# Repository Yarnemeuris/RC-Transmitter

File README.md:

# RC Transmitter

This is an RC Transmitter for controlling things like planes or cars. It's made with a rp2040 microcontroller and a nRf24 ic for the wireless comunication.

## CAD
The transmitter is fully 3D printed and uses about 80g of filament. The parts required for assembly are in the BOM. To assemble it you place M3 nuts and add a screw through them. It was fully designed in onshape, so [you can view it](https://cad.onshape.com/documents/07641ffae3f4ad45f3c4466a/w/8f5604270294a6fafcbc2443/e/dfa80ad51705840b5752194c?renderMode=0&uiState=69ac4f1de3e454b85e083a43).

## PCB
In the transmitter are 2 PCBs. One is a 2 layer board for all the wireless things. The same board can be used to recieve the signals, so you need at least 2 of these.

The other one is 4 layers and has everything else on it: the input, microcontroller, battery management. 

## Firmware
The firmware is setup to transmit everythingvia the second core of the rp2040. This makes sure that it's always available to transmit. The main core does everything else, like drawing to the screen and comunicating with the other ICs. Because this happends on a seperate core, a long I²C message won't stop the transmission. Flashing the board can be done by shorting the two program pads while booting the board, and flashing the [uf2 file](https://github.com/Yarnemeuris/RC-Transmitter/blob/main/Firmware/Firmware.uf2) via the USb connection.

## BOM
This is the simplified BOM. You can find the full and other BOMs [here](https://github.com/Yarnemeuris/RC-Transmitter/tree/main/BOM).

|Category  |Item           |Quantity|Unit Price|Total Price|Running Total|
|----------|---------------|--------|----------|-----------|-------------|
|Components|LCSC Components|1       |$43.52    |$43.52     |$43.52       |
|Components|LCSC Shipping  |1       |$11.44    |$11.44     |$54.96       |
|PCB       |RF PCB         |1       |$2.10     |$2.10      |$57.06       |
|PCB       |Main PCB       |1       |$7.00     |$7.00      |$64.06       |
|PCB       |Stencil        |1       |$12.00    |$12.00     |$76.06       |
|PCB       |JLCPCB Shipping|1       |$20.15    |$20.15     |$96.21       |

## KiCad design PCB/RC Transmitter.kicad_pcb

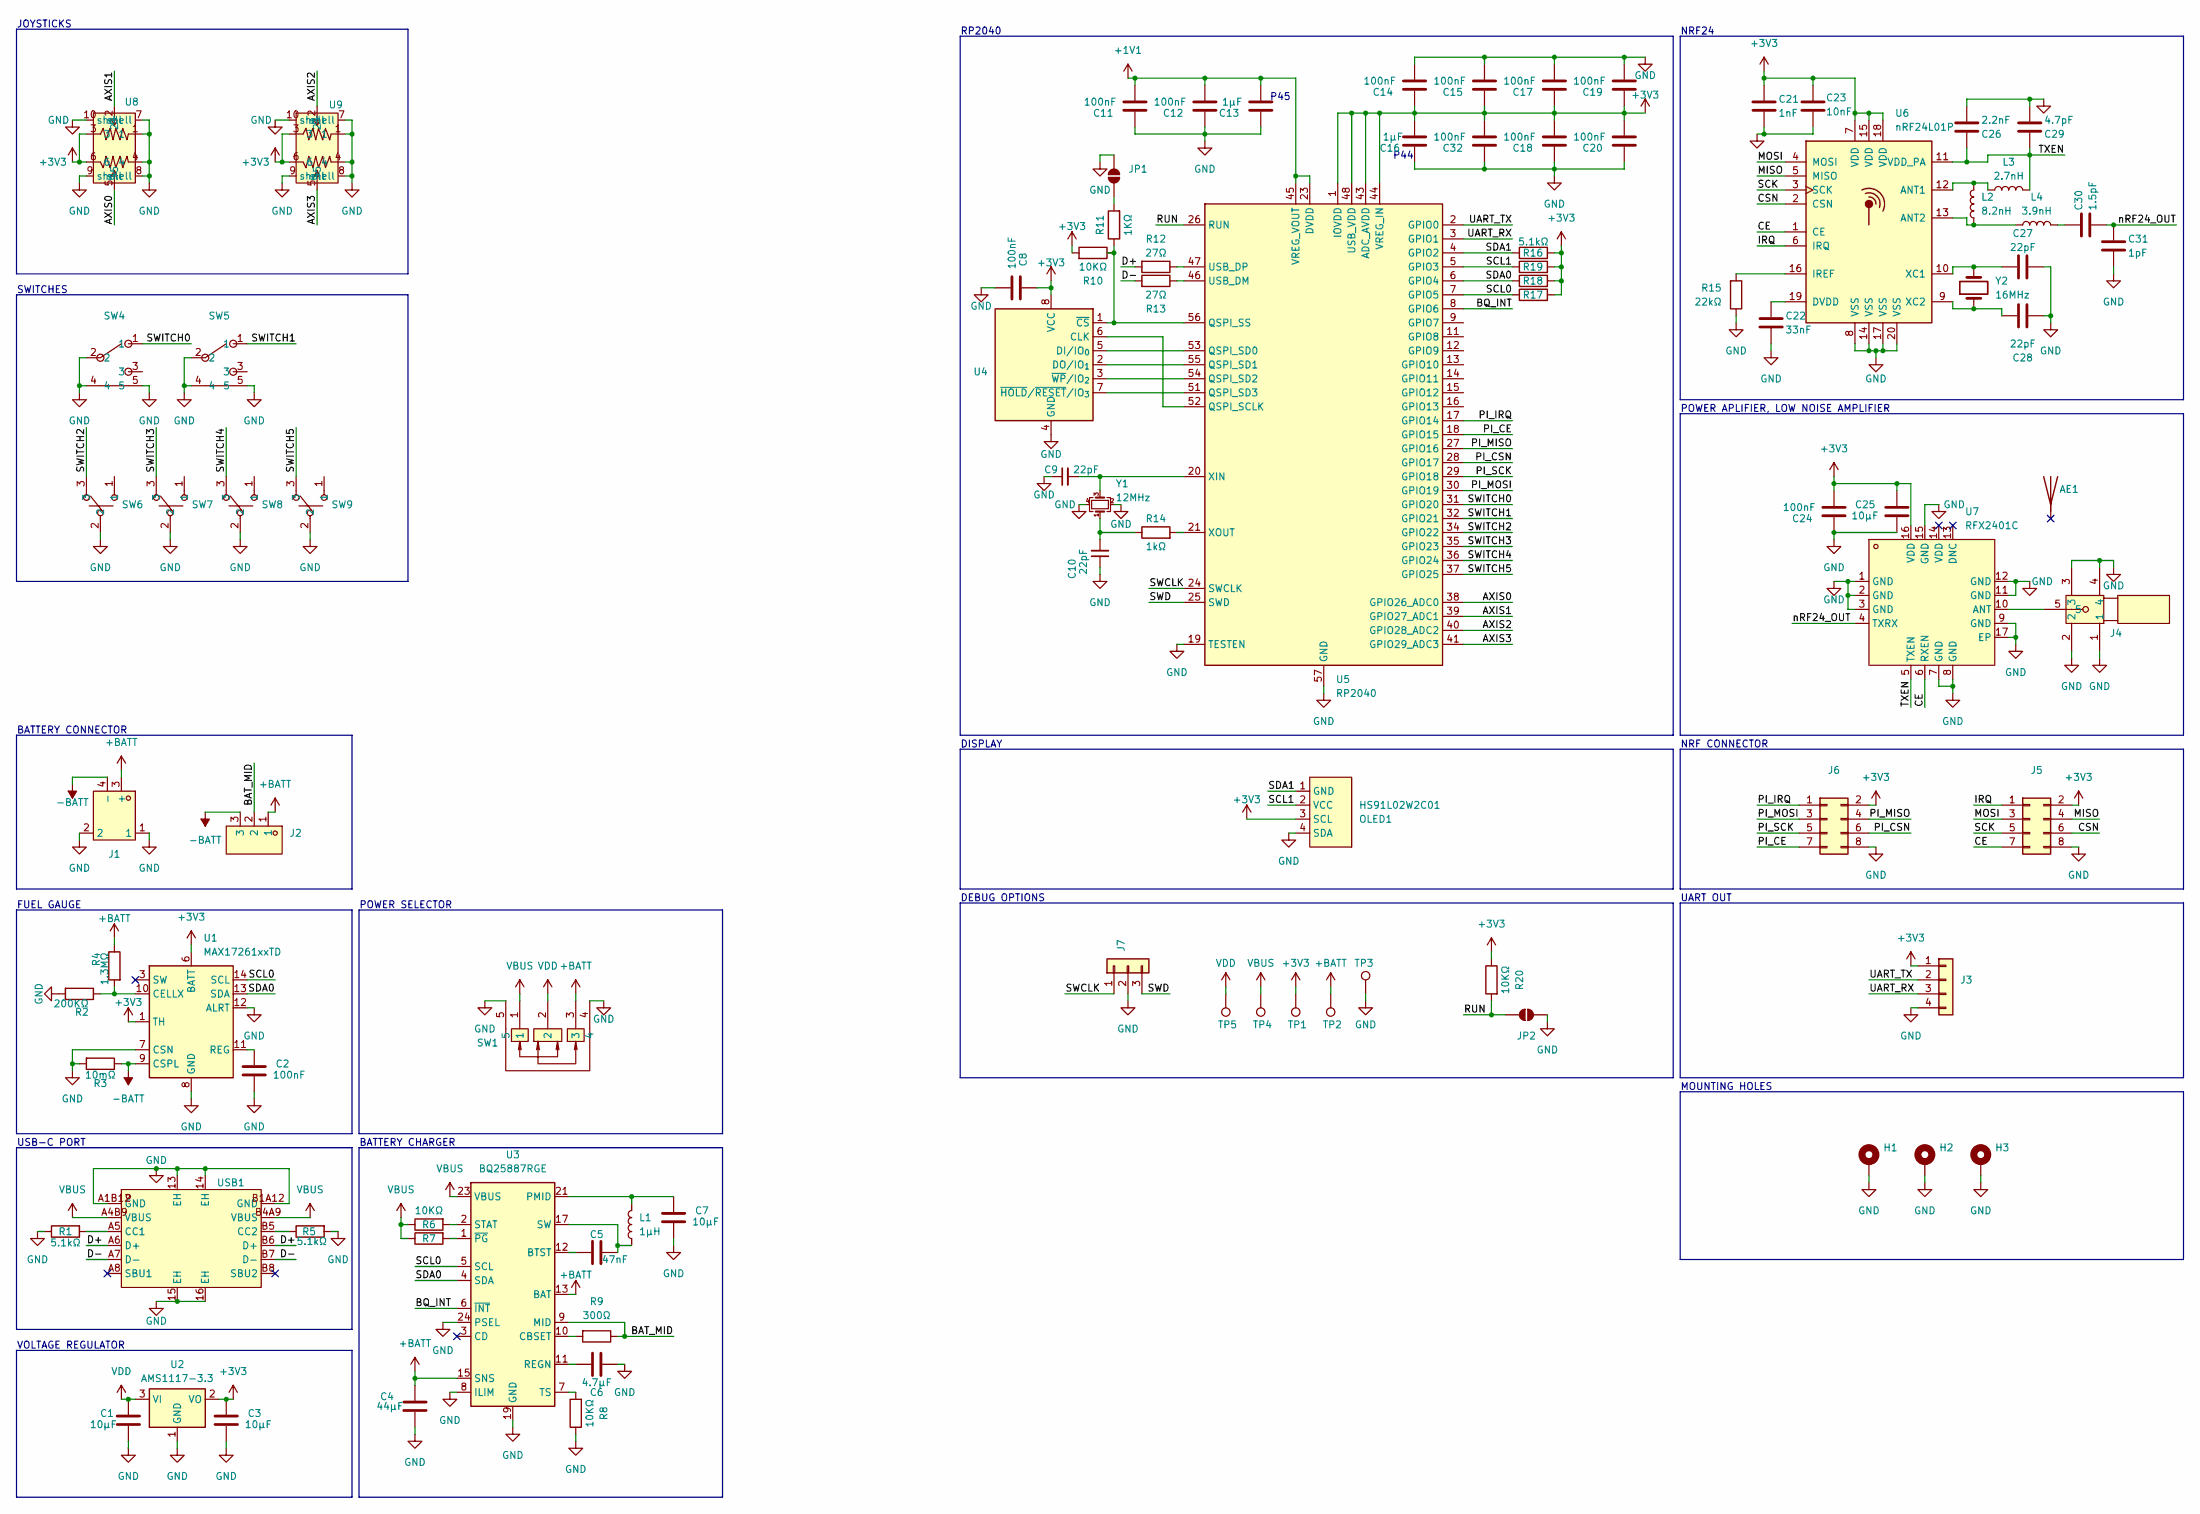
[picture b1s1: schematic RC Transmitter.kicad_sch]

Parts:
AE1: Antenna; SolderJumper-2_P1.3mm_Bridged2Bar_Pad1.0x1.5mm; LCSC Part C497017
C1, C3, C7, C25: 10µF; C_0805_2012Metric; LCSC Part C15850
C2, C8, C11, C12, C14, C15, C17, C18, C19, C20, C24, C32: 100nF; C_0402_1005Metric_Pad0.74x0.62mm_HandSolder; LCSC Part C1525
C4: 44µF; C_1206_3216Metric_Pad1.33x1.80mm_HandSolder; LCSC Part C76659
C5: 47nF; C_0402_1005Metric_Pad0.74x0.62mm_HandSolder; LCSC Part C285062
C6: 4.7µF; C_0402_1005Metric_Pad0.74x0.62mm_HandSolder; LCSC Part C23733
C9, C10: 22pF; C_0402_1005Metric_Pad0.74x0.62mm_HandSolder; LCSC C2176129
C13, C16: 1µF; C_0402_1005Metric_Pad0.74x0.62mm_HandSolder; LCSC Part C14445
C21: 1nF; C_0402_1005Metric_Pad0.74x0.62mm_HandSolder; LCSC Part C106205
C22: 33nF; C_0402_1005Metric_Pad0.74x0.62mm_HandSolder; LCSC Part C106862
C23: 10nF; C_0402_1005Metric_Pad0.74x0.62mm_HandSolder; LCSC Part C15195
C26: 2.2nF; C_0402_1005Metric_Pad0.74x0.62mm_HandSolder; LCSC Part C126534
C27, C28: 22pF; C_0402_1005Metric_Pad0.74x0.62mm_HandSolder; LCSC Part C2176129
C29: 4.7pF; C_0402_1005Metric_Pad0.74x0.62mm_HandSolder; LCSC Part C189469
C30: 1.5pF; C_0402_1005Metric_Pad0.74x0.62mm_HandSolder; LCSC Part C133413
C31: 1pF; C_0402_1005Metric_Pad0.74x0.62mm_HandSolder; LCSC Part C309455
H1, H2, H3: MountingHole_Pad; MountingHole_3.2mm_M3_Pad
J1: XT60PW-F_C428722; TH_2P-XT60PW-F; LCSC Part C428722
J2: HX25418-3WA; CONN-TH_HX25418-3WA; LCSC Part C704579
J3: Conn_01x04; PinHeader_1x04_P2.54mm_Vertical; LCSC Part C32713270
J4: BWSMA-KWE-Z001; SMA-TH_BWSMA-KWE-Z001; LCSC Part C496551
J5: Conn_02x04_Odd_Even; PinHeader_2x04_P2.54mm_Horizontal; LCSC Part C7501296
J6: Conn_02x04_Odd_Even; PinSocket_2x04_P2.54mm_Horizontal; LCSC Part C19268754
J7: Conn_01x03; SolderWire-0.75sqmm_1x03_P7mm_D1.25mm_OD3.5mm
JP1, JP2: SolderJumper_2_Open; SolderJumper-2_P1.3mm_Open_RoundedPad1.0x1.5mm
L1: 1µH; L_0402_1005Metric_Pad0.77x0.64mm_HandSolder; LCSC Part C531288
L2: 8.2nH; L_0402_1005Metric_Pad0.77x0.64mm_HandSolder; LCSC Part C98066
L3: 2.7nH; L_0402_1005Metric_Pad0.77x0.64mm_HandSolder; LCSC Part C142181
L4: 3.9nH; L_0402_1005Metric_Pad0.77x0.64mm_HandSolder; LCSC Part C186820
OLED1: HS91L02W2C01; OLED-TH_L38.0-W12.0_HS91L02W2C01; LCSC Part C5248081
R1, R5, R16, R17, R18, R19: 5.1kΩ; R_0402_1005Metric_Pad0.72x0.64mm_HandSolder; LCSC C2906874
R2: 200KΩ; R_0402_1005Metric_Pad0.72x0.64mm_HandSolder; LCSC C114763
R3: 10mΩ; R_1206_3216Metric_Pad1.30x1.75mm_HandSolder; LCSC C7467248
R4: 1.3MΩ; R_0402_1005Metric_Pad0.72x0.64mm_HandSolder; LCSC C203121
R6, R7, R8, R10, R20: 10KΩ; R_0402_1005Metric_Pad0.72x0.64mm_HandSolder; LCSC Part C60490
R9: 300Ω; R_1206_3216Metric_Pad1.30x1.75mm_HandSolder; LCSC Part C3013269
R11: 1KΩ; R_0402_1005Metric_Pad0.72x0.64mm_HandSolder; LCSC Part C106235
R12, R13: 27Ω; R_0402_1005Metric_Pad0.72x0.64mm_HandSolder; LCSC Part C138021
R14: 1kΩ; R_0402_1005Metric_Pad0.72x0.64mm_HandSolder; LCSC C106235
R15: 22kΩ; R_0402_1005Metric_Pad0.72x0.64mm_HandSolder; LCSC Part C2909337
SW1: SS-12D11G5R; SW-TH_SS-12D11G5R; LCSC Part C388633
SW4, SW5: MT-0-102-C004-N004-RS; SW-TH_MT-0-102-C004-N004-RS; LCSC Part C1788496
SW6, SW7, SW8, SW9: 2AS3T1A1M2QES; SW-TH_2AS3T1A1M2QES; LCSC Part C908284
TP1, TP2, TP3, TP4, TP5: TestPoint; TestPoint_Pad_D2.5mm
U1: MAX17261xxTD; TDFN-14-1EP_3x3mm_P0.4mm_EP1.78x2.35mm; LCSC Part C7457893
U2: AMS1117-3.3; SOT-223-3_TabPin2; LCSC Part C347222
U3: BQ25887RGE; Texas_RGE0024H_VQFN-24-1EP_4x4mm_P0.5mm_EP2.7x2.7mm_Thermal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; LCSC Part C2761614
U4: W25Q128JVS; SOIC-8_5.3x5.3mm_P1.27mm; LCSC Part C401671
U5: RP2040; QFN-56-1EP_7x7mm_P0.4mm_EP3.2x3.2mm; LCSC Part C2040
U6: nRF24L01P; QFN-20-1EP_4x4mm_P0.5mm_EP2.5x2.5mm; LCSC Part C8791
U7: RFX2401C; QFN-16_L3.0-W3.0-P0.50-BL-EP1.7; LCSC Part C19213
U8: YF16-DFL7.2-B5KO(45-10)B5KO(55)-RG-A22; JOYTICK-TH_YF16-DFL7.2-B5KO-45-10-B5KO-55--RG-A22; LCSC Part C37323741
U9: YF16-FL7.2-B5KA(45-10)-R-A28; JOYTICK-TH_YF16-DFL7.2-B5KO-45-10-B5KO-55--RG-A22; LCSC Part C37323739
USB1: GT-USB-7070A01; USB-SMD_GT-USB-7070A01; LCSC Part C5446865
Y1: 12MHz; Crystal_SMD_3225-4Pin_3.2x2.5mm; LCSC Part C9002
Y2: 16MHz; Crystal_Round_D3.0mm_Vertical; LCSC Part C2836024

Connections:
+1V1: C11.1, C12.1, C13.1, U5.23 (DVDD), U5.45 (VREG_VOUT), U5.50 (DVDD)
+3V3: C3.2, C8.2, C14.2, C15.2, C16.1, C17.2, C18.1, C19.2, C20.1, C21.2, C23.2, C24.1, C25.2, C32.1, J3.1, J5.2, J6.2, OLED1.3 (SCL), R10.2, R16.2, R17.2, R18.2, R19.2, R20.1, TP1.1, U1.1 (TH), U1.6 (BATT), U2.2 (VO), U4.8 (VCC), U5.1 (IOVDD), U5.10 (IOVDD), U5.22 (IOVDD), U5.33 (IOVDD), U5.42 (IOVDD), U5.43 (ADC_AVDD), U5.44 (VREG_IN), U5.48 (USB_VDD), U5.49 (IOVDD), U6.7 (VDD), U6.15 (VDD), U6.18 (VDD), U7.16 (VDD), U8.3, U8.6, U9.3, U9.6
+BATT: C4.2, J1.3 (+), J2.1, R4.1, SW1.3, TP2.1, U3.13 (BAT), U3.14 (BAT), U3.15 (SNS), U3.16 (SNS)
-BATT: J1.4 (-), J2.3, R3.1, U1.9 (CSPL)
/AXIS0: U5.38 (GPIO26_ADC0), U8.5
/AXIS1: U5.39 (GPIO27_ADC1), U8.2
/AXIS2: U5.40 (GPIO28_ADC2), U9.2
/AXIS3: U5.41 (GPIO29_ADC3), U9.5
/BAT_MID: J2.2, R9.1, U3.9 (MID)
/BQ_INT: U3.6 (~INT), U5.8 (GPIO6)
/CE: J5.7, U6.1 (CE), U7.6 (RXEN)
/CSN: J5.6, U6.2 (CSN)
/D+: R12.2, USB1.A6 (D+), USB1.B6 (D+)
/D-: R13.2, USB1.A7 (D-), USB1.B7 (D-)
/IRQ: J5.1, U6.6 (IRQ)
/MISO: J5.4, U6.5 (MISO)
/MOSI: J5.3, U6.4 (MOSI)
/PI_CE: J6.7, U5.18 (GPIO15)
/PI_CSN: J6.6, U5.28 (GPIO17)
/PI_IRQ: J6.1, U5.17 (GPIO14)
/PI_MISO: J6.4, U5.27 (GPIO16)
/PI_MOSI: J6.3, U5.30 (GPIO19)
/PI_SCK: J6.5, U5.29 (GPIO18)
/RUN: JP2.1 (A), R20.2, U5.26 (RUN)
/SCK: J5.5, U6.3 (SCK)
/SCL0: R17.1, U1.14 (SCL), U3.5 (SCL), U5.7 (GPIO5)
/SCL1: OLED1.2 (VCC), R19.1, U5.5 (GPIO3)
/SDA0: R18.1, U1.13 (SDA), U3.4 (SDA), U5.6 (GPIO4)
/SDA1: OLED1.1 (GND), R16.1, U5.4 (GPIO2)
/SWCLK: J7.1, U5.24 (SWCLK)
/SWD: J7.3, U5.25 (SWD)
/SWITCH0: SW4.1, U5.31 (GPIO20)
/SWITCH1: SW5.1, U5.32 (GPIO21)
/SWITCH2: SW6.3, U5.34 (GPIO22)
/SWITCH3: SW7.3, U5.35 (GPIO23)
/SWITCH4: SW8.3, U5.36 (GPIO24)
/SWITCH5: SW9.3, U5.37 (GPIO25)
/TXEN: C26.2, C29.2, L3.2, U6.11 (VDD_PA), U7.5 (TXEN)
/UART_RX: J3.3, U5.3 (GPIO1)
/UART_TX: J3.2, U5.2 (GPIO0)
/nRF24_OUT: C30.1, C31.2, U7.4 (TXRX)
GND: C1.1, C2.1, C3.1, C4.1, C6.1, C7.1, C8.1, C9.1, C10.1, C11.2, C12.2, C13.2, C14.1, C15.1, C16.2, C17.1, C18.2, C19.1, C20.2, C21.1, C22.1, C23.1, C24.2, C25.1, C26.1, C27.2, C28.2, C29.1, C31.1, C32.2, H1.1, H2.1, H3.1, J1.1, J1.2, J3.4, J4.1, J4.2, J4.3, J4.4, J5.8, J6.8, J7.2, JP1.1 (A), JP2.2 (B), OLED1.4 (SDA), R1.1, R2.2, R3.2, R5.2, R8.1, R15.1, SW1.4, SW1.5, SW4.2, SW4.4, SW4.5, SW5.2, SW5.4, SW5.5, SW6.2, SW7.2, SW8.2, SW9.2, TP3.1, U1.7 (CSN), U1.8 (GND), U1.12 (ALRT), U1.15 (GND), U2.1 (GND), U3.8 (ILIM), U3.19 (GND), U3.20 (GND), U3.24 (PSEL), U3.25 (GND), U4.4 (GND), U5.19 (TESTEN), U5.57 (GND), U6.8 (VSS), U6.14 (VSS), U6.17 (VSS), U6.20 (VSS), U6.21 (EP), U7.1 (GND), U7.2 (GND), U7.3 (GND), U7.7 (GND), U7.8 (GND), U7.9 (GND), U7.11 (GND), U7.12 (GND), U7.15 (GND), U7.17 (EP), U8.1, U8.4, U8.7 (shell), U8.8 (shell), U8.9 (shell), U8.10 (shell), U9.1, U9.4, U9.7 (shell), U9.8 (shell), U9.9 (shell), U9.10 (shell), USB1.13 (EH), USB1.14 (EH), USB1.15 (EH), USB1.16 (EH), USB1.A1B12 (GND), USB1.B1A12 (GND), Y1.2, Y1.4
unnamed: C5.2, L1.1, U3.17 (SW), U3.18 (SW)
unnamed: C7.2, L1.2, U3.21 (PMID), U3.22 (PMID)
unnamed: C10.2, R14.1, Y1.1
unnamed: C30.2, L4.2
unnamed: JP1.2 (B), R11.2
unnamed: R2.1, R4.2, U1.10 (CELLX)
unnamed: C2.2, U1.11 (REG)
unnamed: C5.1, U3.12 (BTST)
unnamed: R9.2, U3.10 (CBSET)
unnamed: C6.2, U3.11 (REGN)
unnamed: R6.2, U3.2 (STAT)
unnamed: R8.2, U3.7 (TS)
unnamed: R7.2, U3.1 (~PG)
unnamed: U4.6 (CLK), U5.52 (QSPI_SCLK)
unnamed: U4.5 (DI/IO_{0}), U5.53 (QSPI_SD0)
unnamed: U4.2 (DO/IO_{1}), U5.55 (QSPI_SD1)
unnamed: R10.1, R11.1, U4.1 (~CS), U5.56 (QSPI_SS)
unnamed: U4.7 (~HOLD/~RESET/IO_{3}), U5.51 (QSPI_SD3)
unnamed: U4.3 (~WP/IO_{2}), U5.54 (QSPI_SD2)
unnamed: R13.1, U5.46 (USB_DM)
unnamed: R12.1, U5.47 (USB_DP)
unnamed: C9.2, U5.20 (XIN), Y1.3
unnamed: R14.2, U5.21 (XOUT)
unnamed: L2.2, L3.1, U6.12 (ANT1)
unnamed: L2.1, L4.1, U6.13 (ANT2)
unnamed: C22.2, U6.19 (DVDD)
unnamed: R15.2, U6.16 (IREF)
unnamed: C27.1, U6.10 (XC1), Y2.2
unnamed: C28.1, U6.9 (XC2), Y2.1
unnamed: J4.5, U7.10 (ANT)
unnamed: R1.2, USB1.A5 (CC1)
unnamed: R5.1, USB1.B5 (CC2)
VBUS: R6.1, R7.1, SW1.1, TP4.1, U3.23 (VBUS), USB1.A4B9 (VBUS), USB1.B4A9 (VBUS)
VDD: C1.2, SW1.2, TP5.1, U2.3 (VI)

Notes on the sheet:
P45
POWER APLIFIER, LOW NOISE AMPLIFIER
NRF24
USB-C PORT
BATTERY CONNECTOR
VOLTAGE REGULATOR
JOYSTICKS
DEBUG OPTIONS
RP2040
POWER SELECTOR
MOUNTING HOLES
NRF CONNECTOR
BATTERY CHARGER
P44
DISPLAY
UART OUT
FUEL GAUGE
SWITCHES

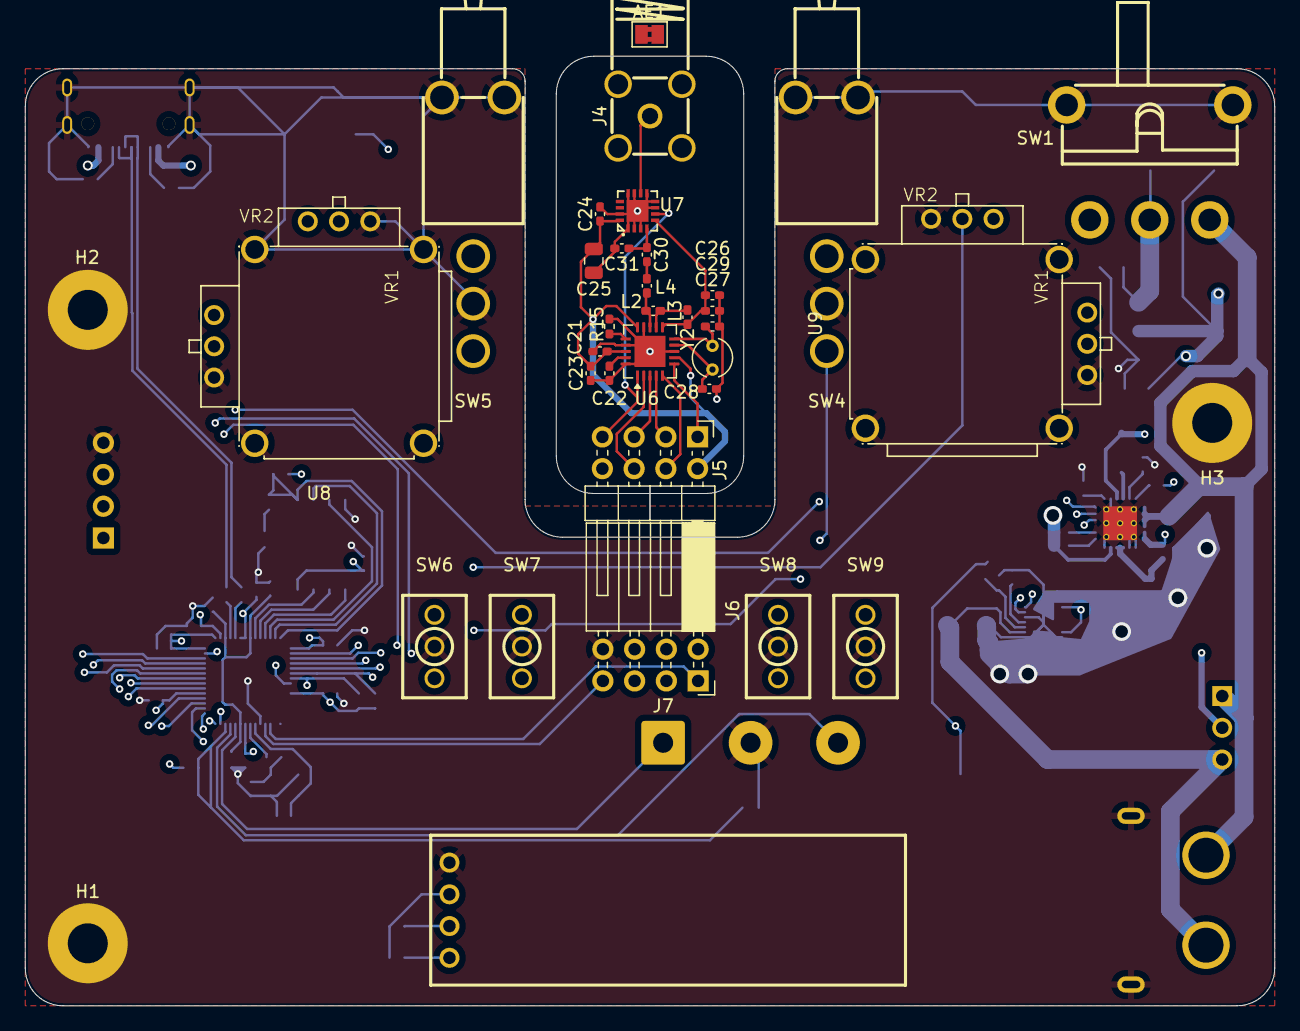
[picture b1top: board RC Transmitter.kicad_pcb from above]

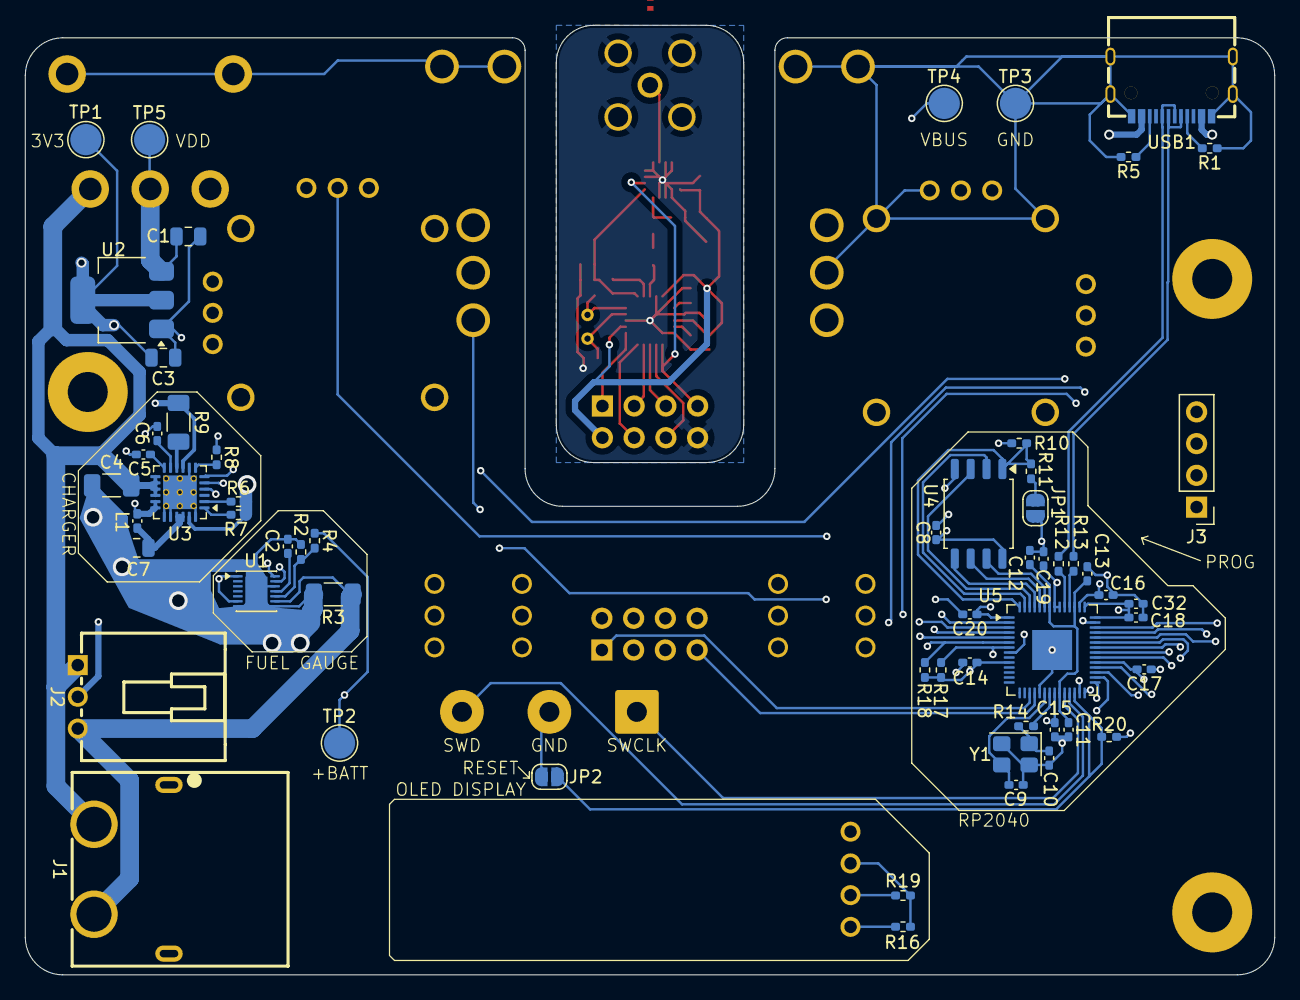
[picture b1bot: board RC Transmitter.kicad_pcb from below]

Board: 4 copper layers, 100.0 x 76.0 mm, 94 parts (58 on the bottom side), 76 nets.

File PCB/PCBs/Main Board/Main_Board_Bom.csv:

Designator,Footprint,Quantity,Value,LCSC Part #
"C1, C3, C7",0805,3,10µF,C15850
"C10, C9",0402,2,22pF,C2176129
"C11, C12, C14, C15, C17, C18, C19, C2, C20, C32, C8",0402,11,100nF,C1525
"C13, C16",0402,2,1µF,C14445
C4,1206,1,44µF,C76659
C5,0402,1,47nF,C285062
C6,0402,1,4.7µF,C23733
J1,TH_2P-XT60PW-F,1,XT60PW-F_C428722,C428722
J2,CONN-TH_HX25418-3WA,1,HX25418-3WA,C704579
J3,PinHeader_1x04_P2.54mm_Vertical,1,Conn_01x04,C32713270
J6,PinSocket_2x04_P2.54mm_Horizontal,1,Conn_02x04_Odd_Even,C19268754
L1,0402,1,1µH,C531288
OLED1,OLED-TH_L38.0-W12.0_HS91L02W2C01,1,HS91L02W2C01,C5248081
"R1, R16, R17, R18, R19, R5",0402,6,5.1kΩ,C2906874
"R10, R20, R6, R7, R8",0402,5,10KΩ,C60490
"R11, R14",0402,2,1KΩ,C106235
"R12, R13",0402,2,27Ω,C138021
R2,0402,1,200KΩ,C114763
R3,1206,1,10mΩ,C7467248
R4,0402,1,1.3MΩ,C203121
R9,1206,1,300Ω,C3013269
SW1,SW-TH_SS-12D11G5R,1,SS-12D11G5R,C388633
"SW4, SW5",SW-TH_MT-0-102-C004-N004-RS,2,MT-0-102-C004-N004-RS,C1788496
"SW6, SW7, SW8, SW9",SW-TH_2AS3T1A1M2QES,4,2AS3T1A1M2QES,C908284
U1,TDFN-14-1EP_3x3mm_P0.4mm_EP1.78x2.35mm,1,MAX17261xxTD,C7457893
U2,SOT-223-3_TabPin2,1,AMS1117-3.3,C347222
U3,Texas_RGE0024H_VQFN-24-1EP_4x4mm_P0.5mm_EP2.7x2.7mm_ThermalVias,1,BQ25887RGE,C2761614
U4,SOIC-8_5.3x5.3mm_P1.27mm,1,W25Q128JVS,C401671
U5,QFN-56-1EP_7x7mm_P0.4mm_EP3.2x3.2mm,1,RP2040,C2040
U8,JOYTICK-TH_YF16-DFL7.2-B5KO-45-10-B5KO-55--RG-A22,1,YF16-DFL7.2-B5KO(45-10)B5KO(55)-RG-A22,C37323741
U9,JOYTICK-TH_YF16-DFL7.2-B5KO-45-10-B5KO-55--RG-A22,1,YF16-FL7.2-B5KA(45-10)-R-A28,C37323739
USB1,USB-SMD_GT-USB-7070A01,1,GT-USB-7070A01,C5446865
Y1,Crystal_SMD_3225-4Pin_3.2x2.5mm,1,12MHz,C9002

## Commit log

2026-02-14 made the PCB
2026-02-14 input and transmission firmware
2026-02-18 PCB update see journal for more information
2026-02-18 moved transmission and input to second core (with only a little spaghetti)
2026-02-19 display information on the screen
2026-03-05 Code changes
2026-03-05 PCB upadte
2026-03-22 Changed repo layout
2026-03-22 Added BOMs
2026-03-22 Added an extra image
2026-03-22 Add links in README
    Updated image references and added links for firmware and BOM.
2026-03-22 Added link to PCB files
2026-03-22 CAD changes
2026-03-22 .STEP changed too ofc
